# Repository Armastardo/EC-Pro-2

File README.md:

# EC Pro2

Open source HHKB Pro2 Controller and mainboard.

## **MODIFIED**

This is a modification of the board made by Cipulot. The only change is a different footprint to use the [USB1130-15-A](https://www.mouser.com/ProductDetail/640-USB1130-15-A) port since the original part it's no longer available and I couldn't find a proper replacement anywhere. The back side of the PCB also contains the URL to this repository and some text to acknowledge the difference. The port is not available at LCSC so you'll need to order separately and solder yourself. It's a THT port so it should be really easy for anyone. Next up is the original text of the repository.

The USB port symbol, footprint and PCB Model were sourced from [snap EDA](https://www.snapeda.com/parts/USB1130-15-A/Global%20Connector%20Technology/view-part/?welcome=home&ref=mouser).

## **DEPRECATED**

Project deprecated in favor of the EC Pro X.

## Introduction

This project is a continuation of my development of open source EC boards.

The supported layout options are the following:

## Technical information

### Mainboard

- Layout size: HHKB Pro2 ANSI and some additions
- Compatible switches: EC switches (Topre and NIZ)
- Microcontroller: STM32F401
- Connector: JST connector for controller board
- Firmware compatibility: QMK (with VIA/VIAL support)
- Protection hardware (present on both the mainboard and both controller versions):
  - Fused
  - ESD protection

### Lite Controller board

The Lite controller board is a slimmed down version of the controller board, featuring only protection hardware and a JST connector for the mainboard.

This is cost effective choice in case the user doesn't need the USB hub feature or the aftermarket case doesn't take advantage of it.

### Normal Controller board

The Normal Controller instead is a full featured controller board, featuring a USB hub, a JST connector for the mainboard and a USB Type-C connector for the PC.

The USB hub is a USB 2.0 hub, featuring 3 USB-A 2.0 ports, one of which is internal, to be used for dongles or small USB drives.

Key features of the Normal Controller are:

- USB 2.0 hub based on the FE1.1 IC
- 2x USB-A 2.0 ports in the same position as the original HHKB Pro 2
- 1x internal USB-A 2.0 port
- Per port current limit on each downstream port using MIC2026-2 for the 2 externally accessible USB ports.

**NOTES**

- The internal USB port is intended only for low power devices, such as dongles and small usb drives as previously mentioned. It is not intended for high power devices. Furthermore it is not ESD protected nor current limited and shares the power rail with the rest of the controller.

- The main USB-C port, as well as the 2x externally accessible USB-A downstream ports are ESD protected and current limited.

Keep in mind the the USB 2.0 power budget sets a typical current limit of **500mA**, therefore that is the total budget available to the entire board (controller + mainboard + devices connected to the hub).

## Renders and Prototypes

### Render

Mainboard:

Lite Controller board:

Normal Controller board:

### Prototypes

Mainboard:

Lite Controller:

Normal Controller:

## Revisions and relative features

### Rev1

This revision implements all the main features of the mainboard ad controllers mentioned in the specifications.

#### Connectivity

The Revision 1 (Rev1) implements a USB hub based on the FE1.1 USB HUB IC.

Connection to the PC is achieved through a USB-C connector while devices downstream will use USB-A ports.

Mind that the USB-C connector is wider than the original USB mini connector used, therefore modifications to enlarge the port cutout on the case will be needed. In case you will use this board in an aftermarket case already designed with USB-C in mind n o further modifications are needed.

#### RGB header

The mainboard features an RGB header for connecting +5V addressable RGB strips. THe properties of the lihting can be controlled through Vial or by assigning RGB control keycodes on the board itself.

On the bottom right corner of the PCB, near the bootloader instructions, a pinout diagram shows how to connect the strip to the header:

#### DFU

To access the DFU mode of the mainboard you can perform one of the following actions:

- press the key to which the `QK_BOOT` keycode is assigned (if available)
- while plugging in the board keep the `ESC` (top left corner key) pressed
- while plugging in the board short the `Boot0` pins on the mainboard

## PCB order procedure

In order to have me highers compatibility possible with PCB manufacturers, I decided to design the board around the [JLC7628 Stackup](https://cart.jlcpcb.com/impedance#:~:text=4%2DLayer%20Impedance%20Control%20Stackup) from JLCPCB.

The rational behind this is that the JCPCB stackup is relatively cheap and if the board worked with the stackup, it would be easier to get the board to work with pretty much any other many that offer an equivalent stackup and higher prices.

Both the `Lite` and `Normal` controllers can be instead be ordered with standard 2 layer stackup.

### Production files

The production can be found in the [Production folder](/Production).

As usual the `*.zip` files are the gerber files, `BOM-*.csv` are the BOM (Bill Of Material) files and `POS-*.csv` are the POS/CPL (Footprint POSition/Component Placement List) files.

## Mainboard

As mentioned above, the mainboard is designed around the JLCPCB stackup. The mainboard is a 4 layer board.

Here are the options to select when ordering the mainboard:

- PCB thickness: 1.6mm
- Impedance: NO
- Layer stackup:
  - L1(Top layer): `EC_Pro2_Mainboard-F_Cu.gbr`
  - L2(Inner layer1): `EC_Pro2_Mainboard-In1_Cu.gbr`
  - L3(Inner layer2): `EC_Pro2_Mainboard-In2_Cu.gbr`
  - L4(Bottom layer): `EC_Pro2_Mainboard-B_Cu.gbr`
- PCB Color: whatever you like
- Surface Finish: whatever you like
- Material Type: `FR-4 TG155`

All the other options can be left as default.

### Assembly options

Here follows the options to be used for assembly:

- Assembly Side: Bottom
- Tooling holes: `Added by JLCPCB`
- Confirm Parts Placement: `yes`

**USB-A connector**

An alternative part that has been tested and works is the `JINJIA USB-SMT-04F-S1-B1-R11` from [LCSC](https://www.lcsc.com/product-detail/USB-Connectors_JINJIA-USB-SMT-04F-S1-B1-R11_C718023.html).

As a general rule of thumb the USB-A connectors are interchangeable if they meet the following requirmemnts:

- fits the PCB outline
- has the same number of pins and mounting
- has the following receptor configuration

  To be more specific, the plastic part of the connector should be on the top and not the bottom.

  **BEWARE** that some USB-A connectors have the plastic part on the bottom, in this case the connector will have the pinout reversed, therefore causing inverse polarity on the USB lines.
  The following picture shows the correct orientation of the USB-A connector on the top board while the incorrect one on the bottom board:

### NOTES ABOUT THE OPTIONS

- Once you upload the gerber files wait for the system to automatically recognize the board outline and layers. It will take a while, be patient.

- `PCB thickness` has been tested on both 1.6mm and 1.2mm so it's your call on which one to use.

- For `Material Type` I strongly suggest to use `FR-4 TG155`, using the standard `FR4-Standard TG130-140` material might result in the board delamination and generally is not advised on 4 layer boards.

## Compatibility notice

The EC Pro2 project is intended as a full replacement kit for the OEM HHKB Pro2 controller and main PCB. Therefore it **IS NOT** compatible with the OEM PCBs (both controller and mainboard).

## Copyright notice

This project is not endorse nor sponsored in any way by Topre Corporation and PFU Limited. The HHKB Logo and Topre logo are trademarks of their respective owners.

## License

<br />This work is licensed under a <a rel="license" href="http://creativecommons.org/licenses/by-nc-sa/4.0/">Creative Commons Attribution-NonCommercial-ShareAlike 4.0 International License</a>.

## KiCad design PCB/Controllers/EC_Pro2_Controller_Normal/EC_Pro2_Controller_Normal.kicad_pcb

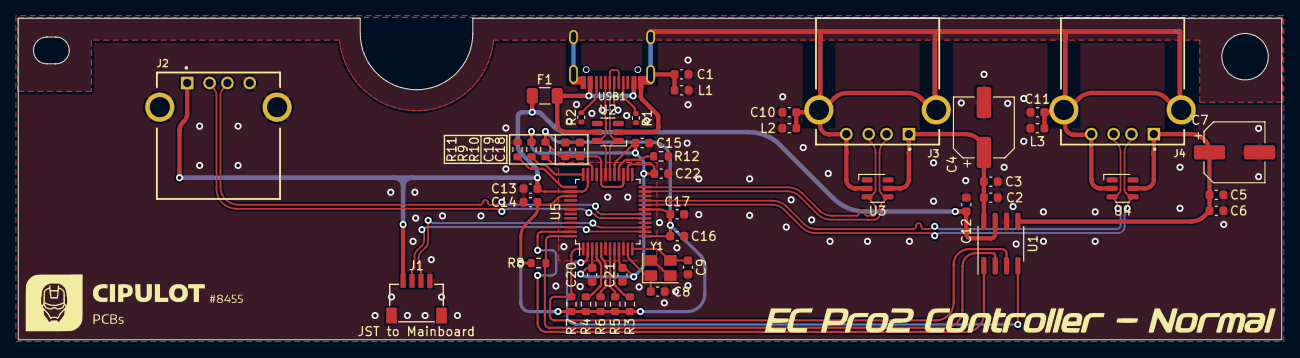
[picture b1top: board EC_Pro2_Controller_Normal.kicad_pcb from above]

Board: 2 copper layers, 141.5 x 36.0 mm, 49 parts (0 on the bottom side), 34 nets.

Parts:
C1, C2, C5, C10, C11, C12, C16, C17, C18, C19, C20, C21, C22: 100n; C_0603_1608Metric
C3, C6, C14, C15: 10u; C_0603_1608Metric
C4, C7: 100u; CP_Elec_6.3x5.9
C8, C9: 30p; C_0603_1608Metric
C13: 1u; C_0603_1608Metric
F1: 500mA; Fuse_1206_3216Metric
J1: JST; JST-SR-4
J2, J3, J4: USB_A; GCT_USB1130-15-A_REVA
L1, L2, L3: 220 @ 100MHz, 2A; L_0603_1608Metric
R1, R2: 5.1k; R_0402_1005Metric
R3, R4, R5, R6, R7, R8, R9, R10, R11: 10k; R_0603_1608Metric
R12: 2.7K; R_0603_1608Metric
U1: MIC2026-2BM; SOIC-8_3.9x4.9mm_P1.27mm
U2, U3, U4: SRV05-4; SOT-23-6-routable
U5: FE1.1; LQFP-48_7x7mm_P0.5mm
USB1: HRO-TYPE-C-31-M-12; HRO-TYPE-C-31-M-12-Assembly
Y1: 12MHz; Crystal_SMD_3225-4pin_3.2x2.5mm

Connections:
+1V8: C15.1, C20.1, C21.1, C22.1, R9.1, U5.3 (VD18), U5.9 (VD_PLL), U5.26 (VREG18), U5.29 (VD18)
+3V3: C14.1, C16.1, C17.1, C18.1, C19.1, R3.1, R4.1, R5.1, R6.1, R7.1, R8.1, R10.1, U5.13 (VD33), U5.19 (VD33), U5.27 (VD3_IN), U5.32 (VD33), U5.39 (VD33_OUT), U5.41 (VD33)
/BUS_B: R9.2, U5.36 (BUS_B)
/DIS_REG: R11.1, U5.37 (DIS_REG)
/OVCB1: R8.2, U1.2 (FLGA), U5.48 (OVCB1)
/OVCB2: R7.2, U1.3 (FLGB), U5.1 (OVCB2)
/OVCB3: R6.2, U5.5 (OVCB3)
/OVCB4: R5.2, U5.7 (OVCB4)
/PORT1_PWR: C2.1, C3.1, C4.1, J3.1 (VBUS), U1.8 (OUTA), U3.5 (VP)
/PORT2_PWR: C5.1, C6.1, C7.1, J4.1 (VBUS), U1.5 (OUTB), U4.5 (VP)
/PWRB1: U1.1 (ENA), U5.47 (PWRB1)
/PWRB2: U1.4 (ENB), U5.2 (PWRB2)
/PWRB3: R4.2, U5.4 (PWRB3)
/PWRB4: R3.2, U5.8 (PWRB4)
/~XRSTJ: R10.2, U5.34 (~XRSTJ)
D1+: J3.3 (D+), U3.3 (IO2), U5.24 (DP1)
D1-: J3.2 (D-), U3.4 (IO3), U5.23 (DM1)
D2+: J4.3 (D+), U4.3 (IO2), U5.21 (DP2)
D2-: J4.2 (D-), U4.4 (IO3), U5.20 (DM2)
D3+: J2.3 (D+), U5.18 (DP3)
D3-: J2.2 (D-), U5.17 (DM3)
D4+: J1.3, U5.15 (DP4)
D4-: J1.2, U5.14 (DM4)
D+: U2.6 (IO4), U5.31 (DPU), USB1.6 (DP1), USB1.8 (DP2)
D-: U2.1 (IO1), U5.30 (DMU), USB1.5 (DN2), USB1.7 (DN1)
GND: C1.2, C2.2, C3.2, C4.2, C5.2, C6.2, C7.2, C8.2, C9.2, C10.2, C11.2, C12.2, C13.2, C14.2, C15.2, C16.2, C17.2, C18.2, C19.2, C20.2, C21.2, C22.2, J1.4, J2.4 (GND), J2.S1, J2.S2, L1.2, L2.2, L3.2, R1.1, R2.2, R11.2, R12.2, U1.6 (GND), U5.6 (VSS), U5.10 (VS_PLL), U5.16 (VSS), U5.22 (VSS), U5.25 (VS_A), U5.33 (VSS), U5.40 (TEST), U5.42 (DRV), Y1.2, Y1.4
GNDPWR: C1.1, C10.1, C11.1, J3.4 (GND), J4.4 (GND), L1.1, L2.1, L3.1, U2.2 (VN), U3.2 (VN), U4.2 (VN), USB1.1 (GND), USB1.12 (GND), USB1.13 (SHIELD)
unnamed: R12.1, U5.28 (REXT)
unnamed: R1.2, USB1.4 (CC1)
unnamed: R2.1, USB1.10 (CC2)
VBUS: F1.2, U2.5 (VP), USB1.2 (VBUS), USB1.11 (VBUS)
VCC: C12.1, C13.1, F1.1, J1.1, J2.1 (VBUS), U1.7 (IN), U5.35 (VBUSM), U5.38 (VDD5)
XIN: C9.1, U5.12 (XIN), Y1.3
XOUT: C8.1, U5.11 (XOUT), Y1.1

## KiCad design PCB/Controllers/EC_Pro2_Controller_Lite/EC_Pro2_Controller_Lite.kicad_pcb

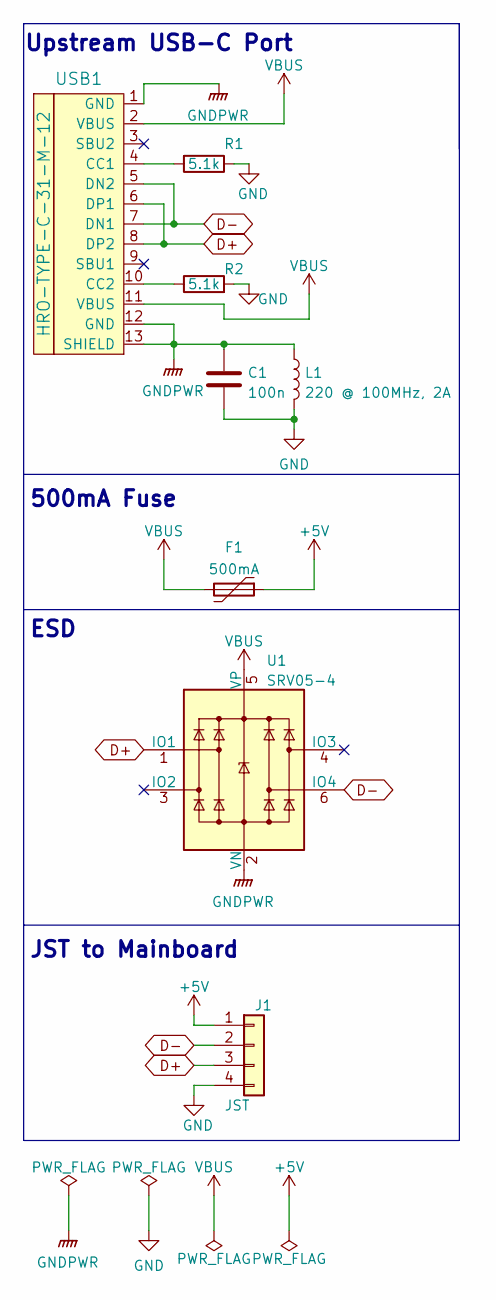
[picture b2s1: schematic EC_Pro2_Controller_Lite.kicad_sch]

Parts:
C1: 100n; C_0603_1608Metric; LCSC C14663
F1: 500mA; Fuse_1206_3216Metric; LCSC C70076
J1: JST; JST-SR-4; LCSC C145956
L1: 220 @ 100MHz, 2A; L_0603_1608Metric; LCSC C85832
R1, R2: 5.1k; R_0402_1005Metric; LCSC C25905
U1: SRV05-4; SOT-23-6-routable; LCSC C85364
USB1: HRO-TYPE-C-31-M-12; HRO-TYPE-C-31-M-12-Assembly; LCSC C165948

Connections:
+5V: F1.1, J1.1
D+: J1.3, U1.1 (IO1), USB1.6 (DP1), USB1.8 (DP2)
D-: J1.2, U1.6 (IO4), USB1.5 (DN2), USB1.7 (DN1)
GND: C1.2, J1.4, L1.2, R1.1, R2.2
GNDPWR: C1.1, L1.1, U1.2 (VN), USB1.1 (GND), USB1.12 (GND), USB1.13 (SHIELD)
unnamed: R1.2, USB1.4 (CC1)
unnamed: R2.1, USB1.10 (CC2)
VBUS: F1.2, U1.5 (VP), USB1.2 (VBUS), USB1.11 (VBUS)

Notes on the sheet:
500mA Fuse
Upstream USB-C Port
ESD
JST to Mainboard

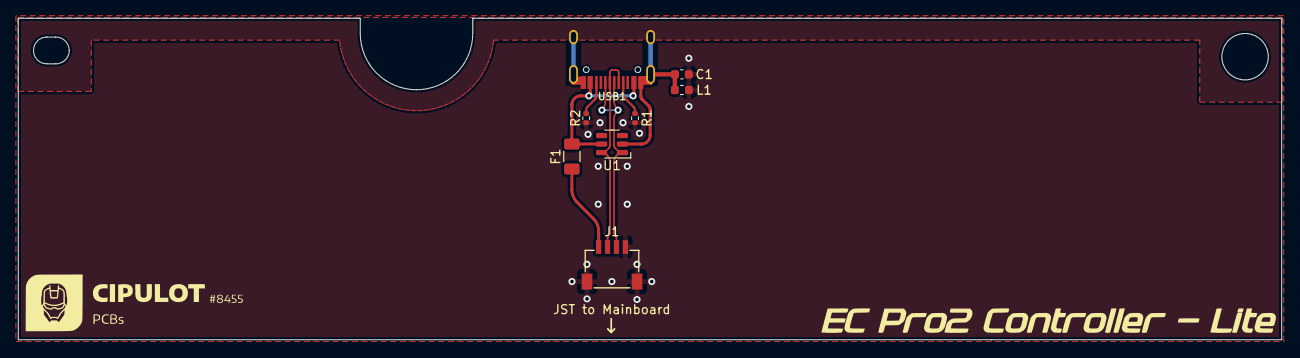
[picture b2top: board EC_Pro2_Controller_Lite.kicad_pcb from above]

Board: 2 copper layers, 141.5 x 36.0 mm, 8 parts (0 on the bottom side), 8 nets.

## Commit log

2022-10-06 Initial Dump
2022-10-06 Updated Mainboard renders
2022-10-06 Assets upload and Readme update
2022-10-14 Update firmware
2022-10-14 Update keymap
2022-10-17 Added pics of mainboard
2022-11-13 Images upload
2022-11-13 Added replacement USB-A secion
2022-11-13 Revert "Added replacement USB-A secion"
    This reverts commit 2c85ad62f3e789279982b1c835f0e04c94be419f.
2022-11-13 Added replacement USB-A section
2022-12-14 Hole position fix
    Small shifting of one of the screw holes to allow for greater tolerance.
2023-01-15 Refactoring of codebase.
2023-03-09 FW Update
    Firmware update.
    Now that the firmware is merged in `master` QMK and also in VIA there's no need to include the `json` file for sideload.
    Use with VIA for now is encouraged, since now the activation threshold function is implemented keyboard-wide with the use of Custom UI VIA V3 elements. Use this feature to tune the actuation in case 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
2023-08-16 Addition of new FW
    New Sideload firmware release that enables new features as:
    - Rapid Trigger (still WIP with bugs)
    - Calibration
    Compatible with previous revisions PCBs.
2023-08-18 AMUX init function consolidation
2023-11-03 Firmware folder update
2023-11-15 Update LICENSE
    Change of License
2023-11-17 Updated sheets
2023-12-21 Update FW
2024-03-03 Update
    Updated the License for the project and relative details.
2024-03-03 Update LICENSE
    Fix formatting
2024-03-12 Replaced type A port to USB1130-15-A

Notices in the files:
PCB/Controllers/EC_Pro2_Controller_Lite/EC_Pro2_Controller_Lite.kicad_pcb:
GNU General Public License v3.0
PCB/Controllers/EC_Pro2_Controller_Normal/EC_Pro2_Controller_Normal.kicad_pcb:
CC-BY-NC-SA-4.0
